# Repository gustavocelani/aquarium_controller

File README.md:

# Aquarium Controller

The propose of this project was develop a aquarium controller capable to control:

* Lights
* Coolers
* Heater
* Temperature
* Cover Status
* Cover Alarm
* Time of Feeding
* Time of Filter Maintense

## Hardware

The MCU used was AtMega2560 presents on Arduino Mega. Also as additional hardware modules and sensors, was used this follows:

* Display Touch Screen LCD TFT 2.4"
* RTC (Real Time Control)
* 4 Rele
* Temperature Sensor DS18B20
* LED Lights
* 2 Coolers 12V
* Aquarium Heater

Each item is describe bellow.

## Display Touch Screen LCD TFT 2.4"

It was used to user do all of interactions with the system.In there was implemented a GUI that make easy any type of command that the user want to do.

## RTC (Real Time Control)

It was used to syncronize all of time functions of the system. Such as time of lights on, time of feeding, periodics maintences and others functions that used any type of syncronism with time.

## 4 Rele Module

Two of four rele was used to coolers, another one was used to LED lights and the last one was used for heater.

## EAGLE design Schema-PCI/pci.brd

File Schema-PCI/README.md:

# Schematic and PCI Layout

You can make your own PCI using this layout.

```
/* *************************************************************
 *
 * Description: Project Schematic and PCI Layout
 *
 * Version: 1
 * Date:    21/06/2016  19:56:03
 * Author:  Gustavo Celani
 *
 * ***********************************************************/

```

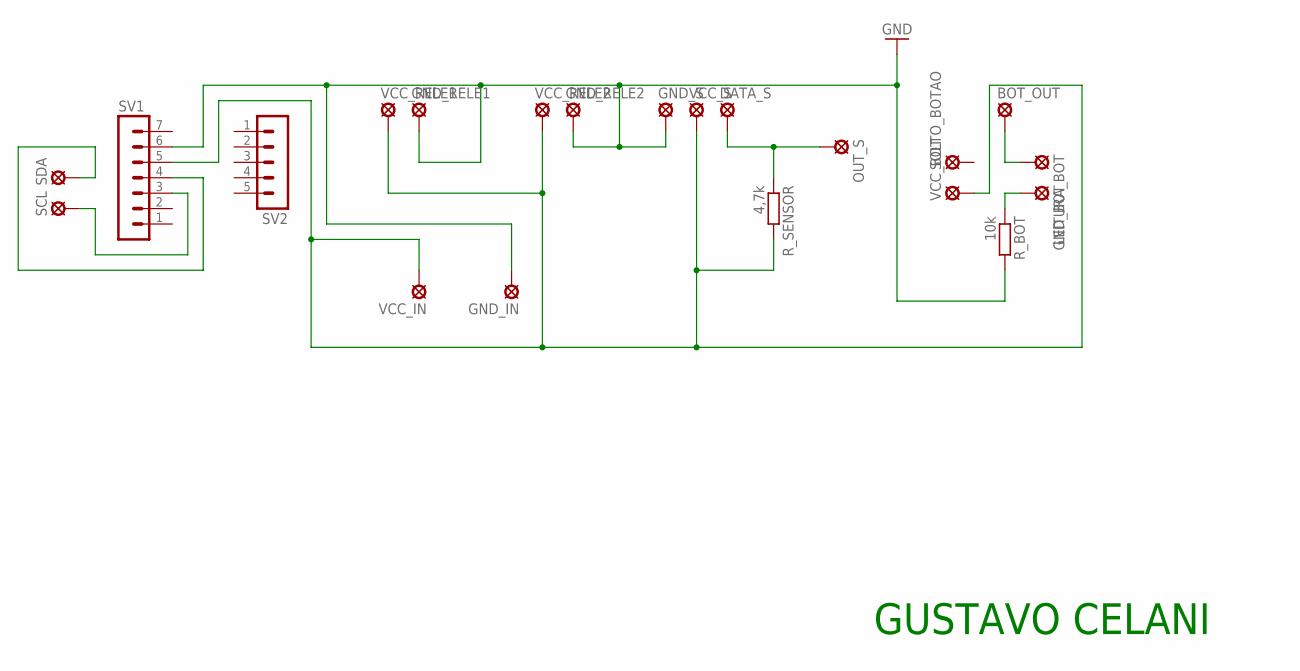
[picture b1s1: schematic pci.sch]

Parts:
BOT_OUT: SE11
DATA_S: SE11
GND_BOT: SE11
GND_IN: SE11
GND_RELE1, GND_RELE2: SE11
GND_S: SE11
LEITURA_BOT: SE11
OUT_S: SE11
R_BOT: 10k; 0204/7
R_SENSOR: 4,7k; 0204/7
SCL: SE11
SDA: SE11
SOLTO_BOTAO: SE11
SV1: MA07-1
SV2: MA05-1
VCC_BOT: SE11
VCC_IN: SE11
VCC_RELE1, VCC_RELE2: SE11
VCC_S: SE11

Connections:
GND: GND_IN.MP, GND_RELE1.MP, GND_RELE2.MP, GND_S.MP, R_BOT.2, SV1.6
unnamed: DATA_S.MP, OUT_S.MP, R_SENSOR.1
unnamed: R_SENSOR.2, SV1.5, VCC_BOT.MP, VCC_IN.MP, VCC_RELE1.MP, VCC_RELE2.MP, VCC_S.MP
unnamed: SCL.MP, SV1.3
unnamed: SDA.MP, SV1.4
unnamed: BOT_OUT.MP, LEITURA_BOT.MP
unnamed: GND_BOT.MP, R_BOT.1

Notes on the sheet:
GUSTAVO CELANI

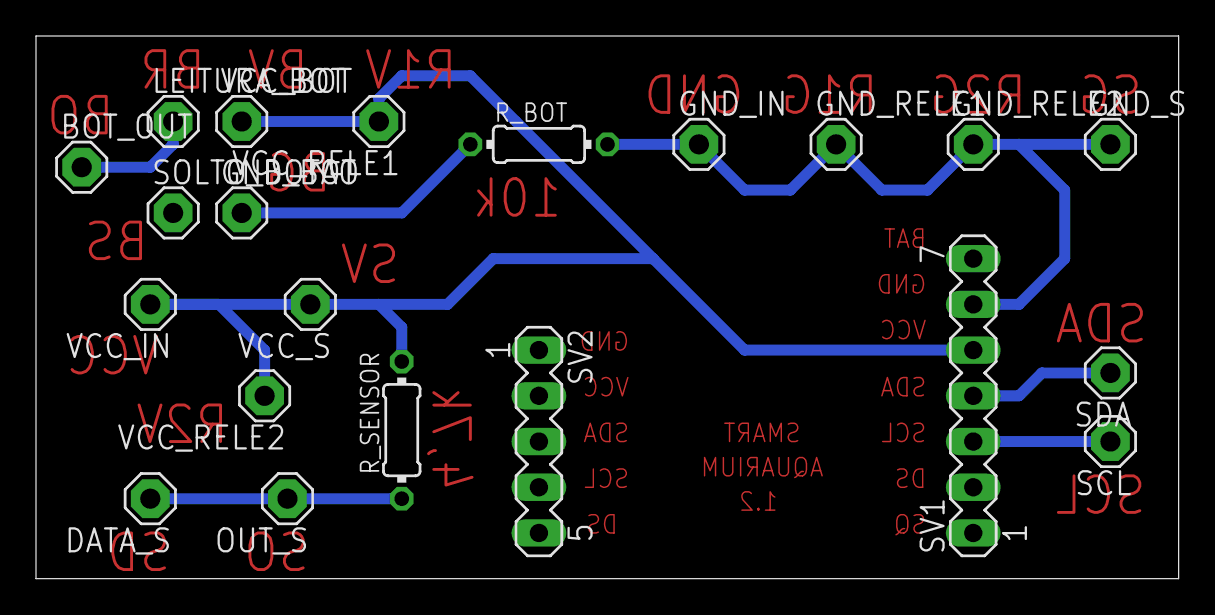
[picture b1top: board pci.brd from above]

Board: 2 copper layers, 63.5 x 30.1 mm, 21 parts (0 on the bottom side), 7 nets.

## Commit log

2018-04-13 Create /src
2018-04-13 Fix srs
2018-04-21 First Commit - Share Project
2018-10-09 External Libraries
2021-04-10 Create LICENSE
